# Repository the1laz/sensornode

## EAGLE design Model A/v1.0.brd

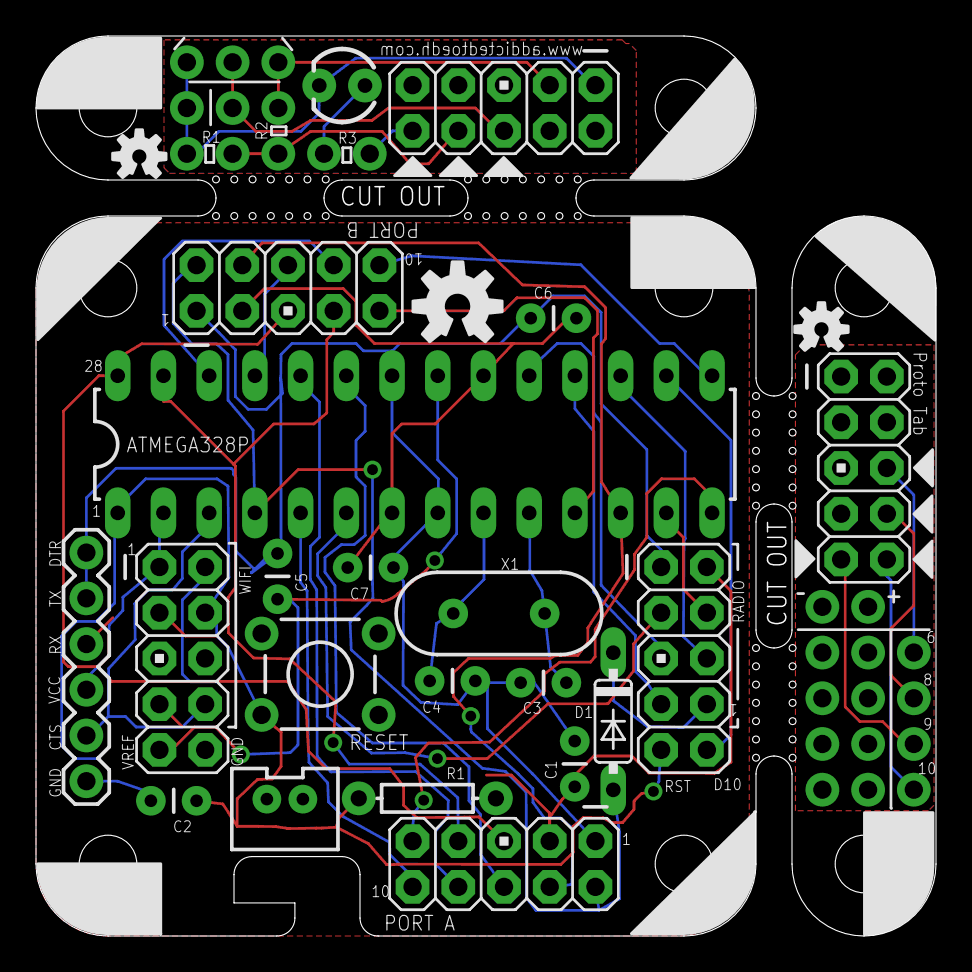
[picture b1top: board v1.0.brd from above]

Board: 2 copper layers, 50.0 x 50.0 mm, 42 parts (0 on the bottom side), 40 nets.

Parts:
C1, C2, C3, C4, C5, C6, C7: CAP-PTH-SMALL
D1: 1N4148DO35-7; DO35-7
JP1, JP2, JP3, JP5, JP8: M05X2PTH; AVR_ICSP
JP4: 1X06
JP6: M02JST-PTH-VERT; JST-2-PTH-VERT
JP7, JP9, JP11: 1X03_NO_SILK
JP10: M021X02_NO_SILK; 1X02_NO_SILK
LED1: LED3MM
Q1: 1X03_NO_SILK
R1: AXIAL-0.3
R2, R3, R4, R5: M021X02_NO_SILK; 1X02_NO_SILK
RESET: SWITCH-MOMENTARY-2PTH; TACTILE-PTH
RF24: M05X2PTH; AVR_ICSP
U1: ATMEGA328P_PDIP; DIL28-3
U$1: DP4040_V1_NOLINES
U$2, U$3: DP4010_V1_NOLINES
U$4: 1X03_NO_SILK
U$5: PI
U$6: OSHW-LOGO-M
U$7, U$8: OSHW-LOGO-S
U$9, U$10, U$11, U$12: PI_XS
Y1: HC49US

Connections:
GND: C1.2, C2.2, C3.2, C5.2, C6.2, C7.2, JP2.1, JP3.1, JP4.1, JP4.2, JP6.2, JP8.2, JP8.10, RESET.1, RF24.1, U1.8, U1.22
GND1: JP1.1, JP10.1
GND2: JP5.1, LED1.K, Q1.3, R3.1, R5.2
unnamed: C2.1, U1.9, Y1.2
unnamed: C4.1, JP8.4, R1.P$2, RESET.3, RF24.9, U1.1
unnamed: C1.1, U1.10, Y1.1
unnamed: RF24.10, U1.16
unnamed: JP2.4, JP3.4, U1.12
unnamed: C5.1, JP8.9, U1.21
unnamed: JP3.9, U1.14
unnamed: D1.A, JP2.2, JP3.2, U1.4
unnamed: JP3.6, U1.23
unnamed: JP3.8, U1.24
unnamed: C4.2, JP4.6
unnamed: JP2.6, U1.25
unnamed: JP2.8, U1.26
unnamed: RF24.6, U1.17
unnamed: JP3.10, U1.5
unnamed: JP4.5, JP8.8, U1.3
unnamed: JP4.4, JP8.1, U1.2
unnamed: RF24.4, U1.13
unnamed: JP2.5, JP3.5, U1.28
unnamed: JP2.7, JP3.7, U1.27
unnamed: RF24.5, U1.19
unnamed: D1.C, RF24.8
unnamed: RF24.3, U1.6
unnamed: RF24.7, U1.18
unnamed: JP2.10, U1.15
unnamed: JP2.9, U1.11
unnamed: JP1.6, JP11.3
unnamed: JP1.8, JP7.3
unnamed: JP1.9, JP9.3
unnamed: JP1.10, U$4.3
unnamed: JP5.10, R2.2
unnamed: LED1.A, R2.1
unnamed: JP5.8, R4.1, R5.1
unnamed: JP5.6, Q1.2, R3.2
VCC: C3.1, C6.1, C7.1, JP2.3, JP3.3, JP4.3, JP6.1, JP8.3, JP8.7, R1.P$1, RF24.2, U1.7, U1.20
VCC1: JP1.3, JP10.2
VCC2: JP5.3, Q1.1, R4.2

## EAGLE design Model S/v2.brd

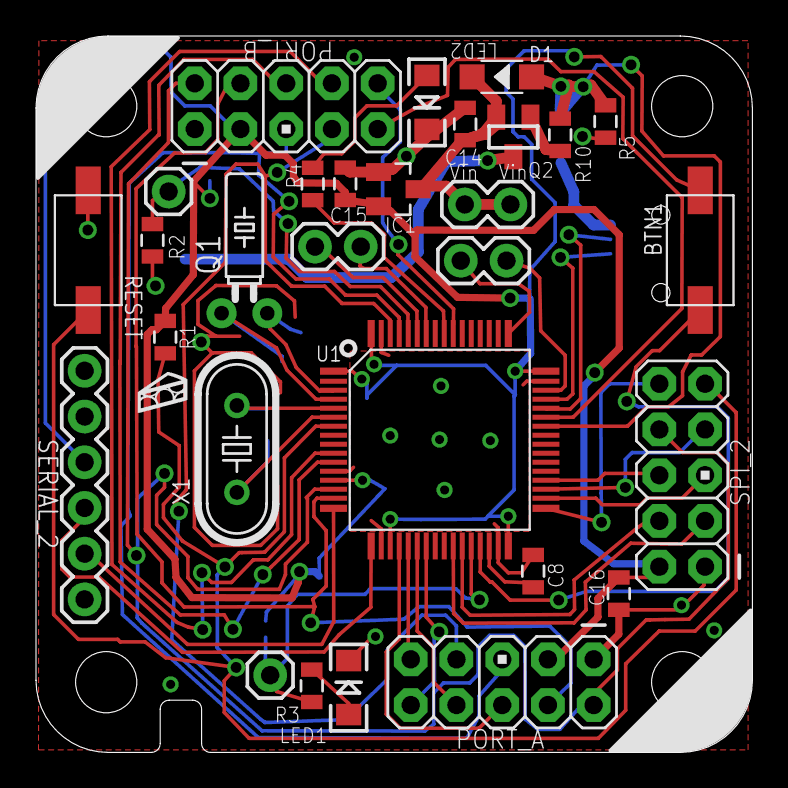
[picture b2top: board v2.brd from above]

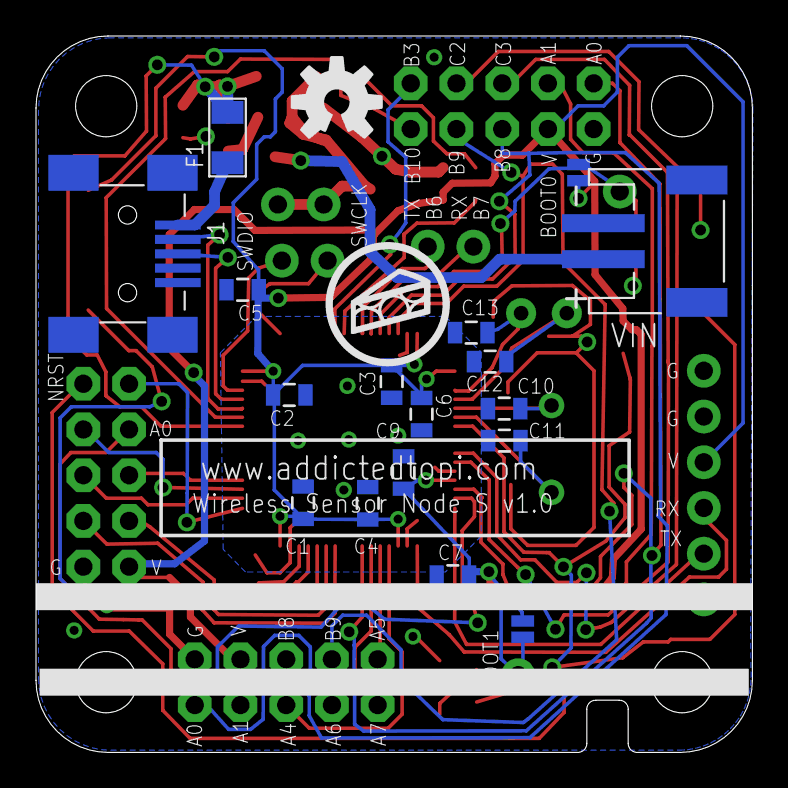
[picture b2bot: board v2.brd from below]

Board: 2 copper layers, 39.8 x 39.8 mm, 49 parts (19 on the bottom side), 45 nets.

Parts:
BTN1: SW2-4.0-6.0X3.0X2.5MM
C1, C2, C3, C4, C5, C6, C7, C8, C9, C10, C11, C12, C13, C14, C15, C16: 0805
D1: 40V-500MA; SOD-123
F1: 500MA; F1206
IC1: MCP1703CB; SOT23
J1: MINIUSB5+4P-SMD-0.8-90D
JP1, JP2, JP10: 1X02
JP3, JP6: 1X01
LED1, LED2: LED-1206
PORT_A: AVR_ICSP
PORT_B: AVR_ICSP
Q1: TC26H
Q2: FDN360P; SUPER-SOT3
R1, R2, R3, R4, R5, R10: 0805
RESET: SW2-4.0-6.0X3.0X2.5MM
SERIAL_2: 1X06
SJ1, SJ2: JUMPER-PAD-2-NO; PAD-JUMPER-2-NO_NO_SILK
SPI_2: AVR_ICSP
U1: LQFP64-0.5-10X10MM
U$1: PI
U$2: OSHW-LOGO-M
U$3: PI_XS
VIN: JST-PH-2-SMT-RA
X1: HC49US

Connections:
5V: C14.2, D1.-, IC1.3, JP10.1, JP10.2, Q2.2
A1: PORT_A.4, PORT_B.4, U1.15
A2: SERIAL_2.5, U1.16
A3: SERIAL_2.4, U1.17
A4: PORT_A.6, U1.20
A5: PORT_A.9, U1.21
A6: PORT_A.8, U1.22
A7: PORT_A.10, U1.23
A10: PORT_B.9, U1.43
B0: SPI_2.3, U1.26
B1: SPI_2.4, U1.27
B2: JP3.1, R3.2, SJ2.2, U1.28
B3: PORT_B.10, U1.55
B4: R4.2, U1.56
B6: JP1.2, U1.58
B7: JP1.1, U1.59
B8: PORT_A.5, PORT_B.5, U1.61
B9: PORT_A.7, PORT_B.7, U1.62
B10: BTN1.1, U1.29
B12: SPI_2.10, U1.33
B13: SPI_2.5, U1.34
B14: SPI_2.7, U1.35
B15: SPI_2.6, U1.36
BOOT0: JP6.1, R2.1, SJ1.1, U1.60
C2: PORT_B.8, U1.10
C3: PORT_B.6, U1.11
GND: C1.2, C2.1, C3.2, C4.2, C5.2, C6.1, C7.1, C8.2, C9.2, C10.1, C11.1, C12.1, C13.1, C14.1, C15.1, C16.1, IC1.1, J1.5, J1.P$1, J1.P$2, J1.P$3, J1.P$4, LED1.C, LED2.C, PORT_A.1, PORT_B.1, R2.2, R5.2, RESET.2, SERIAL_2.1, SERIAL_2.2, SPI_2.1, U1.12, U1.18, U1.31, U1.47, U1.63, VIN.2
INT: PORT_A.2, PORT_B.2, SPI_2.8, U1.14
unnamed: C13.2, Q1.2, U1.3
unnamed: C8.1, U1.30
unnamed: C12.2, Q1.1, U1.4
unnamed: C10.2, U1.5, X1.2
unnamed: C11.2, U1.6, X1.1
unnamed: J1.2, U1.44
unnamed: J1.3, U1.45
unnamed: F1.2, J1.1
unnamed: LED1.A, R3.1
unnamed: LED2.A, R4.1
unnamed: Q2.1, R10.2
NRST: R1.2, RESET.1, SPI_2.9, U1.7
SWCLK: JP2.1, U1.49
SWDIO: JP2.2, U1.46
VDD: BTN1.2, C1.1, C2.2, C3.1, C4.1, C5.1, C6.2, C7.2, C9.1, C15.2, C16.2, IC1.2, PORT_A.3, PORT_B.3, R1.1, SERIAL_2.3, SJ1.2, SJ2.1, SPI_2.2, U1.1, U1.13, U1.19, U1.32, U1.48, U1.64
VIN: Q2.3, VIN.1
VUSB: D1.+, F1.1, R5.1, R10.1, U1.42

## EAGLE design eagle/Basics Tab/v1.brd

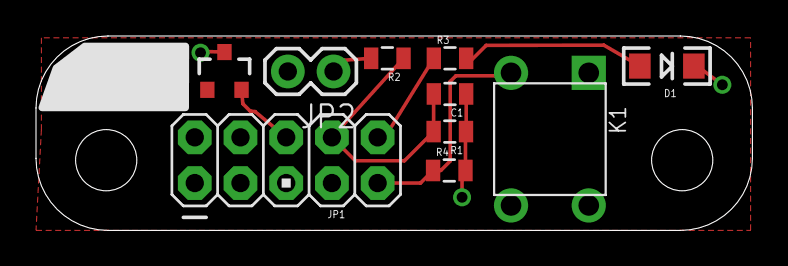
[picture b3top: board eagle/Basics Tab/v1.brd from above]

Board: 2 copper layers, 39.8 x 10.8 mm, 10 parts (0 on the bottom side), 8 nets.

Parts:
C1: 0805
D1: LED-1206
JP1: AVR_ICSP
JP2: 1X02
K1: TS-1109; SW4-6.0X6.0X5.0MM
R1, R2, R3, R4: 0805
U$1: MCP9700SMD; SOT23-3

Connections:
GND: C1.1, D1.C, JP1.1, R1.1, R4.2, U$1.3
unnamed: JP1.9, K1.2, R4.1
unnamed: JP2.1, R2.2
unnamed: D1.A, R3.2
unnamed: JP1.10, R3.1
unnamed: JP1.6, U$1.2
unnamed: C1.2, JP1.8, R1.2, R2.1
VDD: JP1.3, JP2.2, K1.1, U$1.1

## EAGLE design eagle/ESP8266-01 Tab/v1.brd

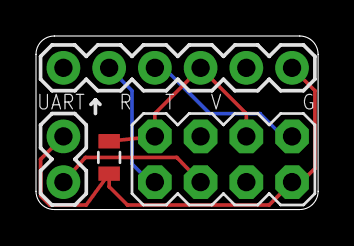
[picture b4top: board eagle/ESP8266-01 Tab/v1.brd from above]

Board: 2 copper layers, 15.7 x 9.6 mm, 4 parts (0 on the bottom side), 5 nets.

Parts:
C1: 0805
JP1: 2X4
JP2: 1X06
SW1: 1X02

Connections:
GND: C1.2, JP1.7, JP2.1, SW1.2
GPIO0: JP1.3, SW1.1
RX: JP1.8, JP2.4
TX: JP1.1, JP2.5
VCC: C1.1, JP1.2, JP1.6, JP2.3

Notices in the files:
parts and their libraries:
SparkFun-Passives: Licensing: Creative Commons ShareAlike 4.0 International - https://creativecommons.org/licenses/by-sa/4.0
